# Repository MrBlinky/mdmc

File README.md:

# MDMC - Menu Driven Multi Cart

A Menu driven Multi Cart for the Atari 2600 made out of a few descrete logic chips and a (E)EPROM or FLASH memory.

Boards can be ordered from [OSH Park](https://oshpark.com/shared_projects/qgWffwwL) or you can create your own using the Eagle board file.

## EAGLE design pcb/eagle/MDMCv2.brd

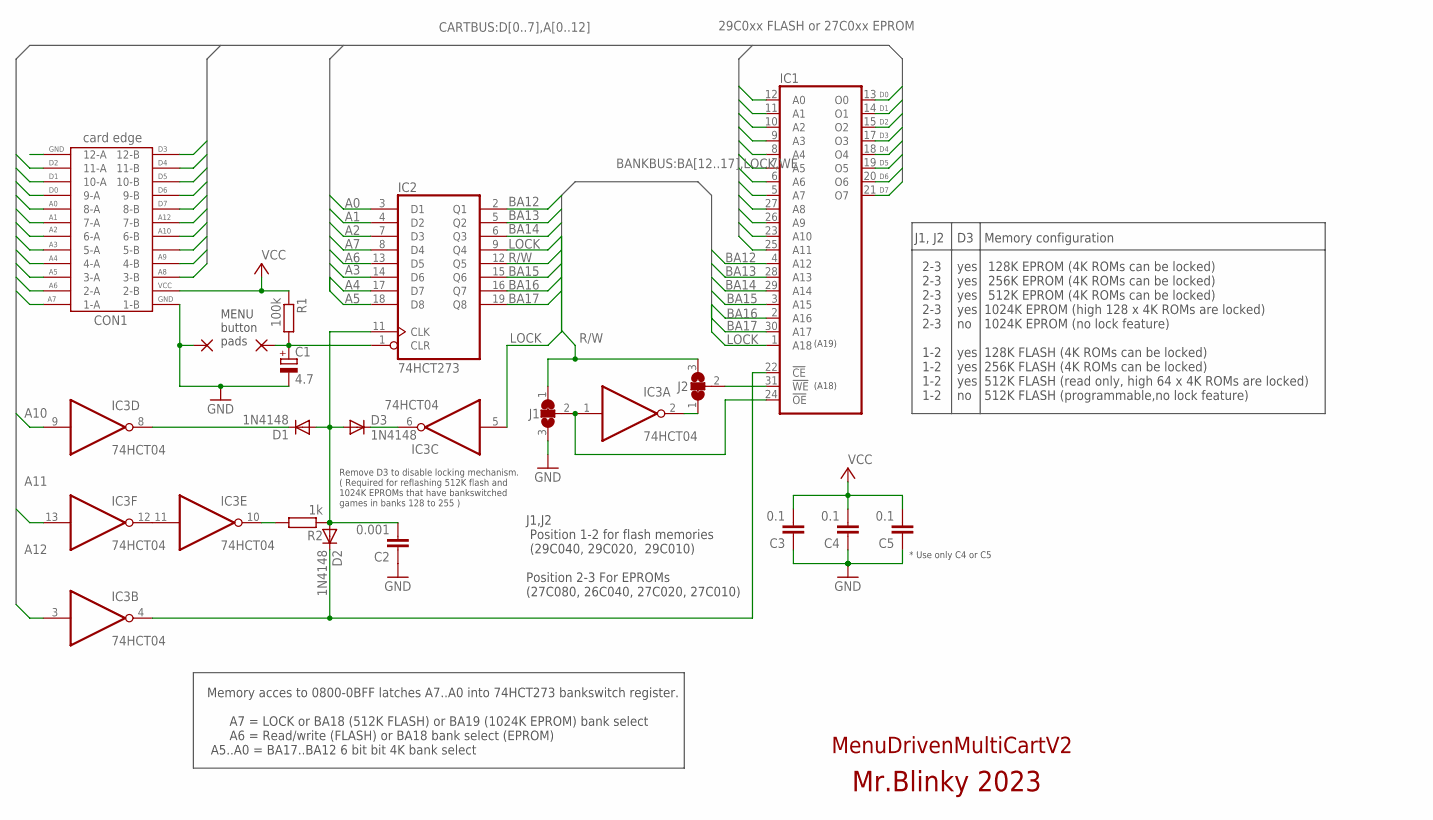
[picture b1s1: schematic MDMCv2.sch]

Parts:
C1: 4.7; TT2D5L
C2: 0.001; C050-025X075
C3, C4, C5: 0.1; C050-025X075
CON1: card edge; 24PINEDGE-254MM
D1, D2, D3: 1N4148; DO35-7
IC1: 29C0xx FLASH or 27C0xx EPROM; DIL32
IC2: 74HCT273; DIL20
IC3: 74HCT04; DIL14
J1, J2: SJ2W; SJ_2
MB1, MB2: WIREPAD1,6/0,9; 1,6/0,9
R1: 100k; 0207/7
R2: 1k; 0207/7

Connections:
!RESET: C1.+, IC2.1 (CLR), MB1.1, R1.2
/A10: D1.C, IC3.8 (O)
/A11: IC3.11 (I), IC3.12 (O)
/CE: D2.C, IC1.22 (!CE), IC3.4 (O)
/LOCK: D3.C, IC3.6 (O)
/OE: IC1.24 (!OE), IC3.1 (I), J1.2
/WE: IC1.31 (!WE), J2.2
/WEJ2: IC3.2 (O), J2.1
A0: CON1.8-A, IC1.12 (A0), IC2.3 (D1)
A1: CON1.7-A, IC1.11 (A1), IC2.4 (D2)
A2: CON1.6-A, IC1.10 (A2), IC2.7 (D3)
A3: CON1.5-A, IC1.9 (A3), IC2.14 (D6)
A4: CON1.4-A, IC1.8 (A4), IC2.17 (D7)
A5: CON1.3-A, IC1.7 (A5), IC2.18 (D8)
A6: CON1.2-A, IC1.6 (A6), IC2.13 (D5)
A7: CON1.1-A, IC1.5 (A7), IC2.8 (D4)
A8: CON1.3-B, IC1.27 (A8)
A9: CON1.4-B, IC1.26 (A9)
A10: CON1.6-B, IC1.23 (A10), IC3.9 (I)
A11: CON1.5-B, IC1.25 (A11), IC3.13 (I)
A11B: IC3.10 (O), R2.2
A12: CON1.7-B, IC3.3 (I)
BA12: IC1.4 (A12), IC2.2 (Q1)
BA13: IC1.28 (A13), IC2.5 (Q2)
BA14: IC1.29 (A14), IC2.6 (Q3)
BA15: IC1.3 (A15), IC2.15 (Q6)
BA16: IC1.2 (A16), IC2.16 (Q7)
BA17: IC1.30 (A17), IC2.19 (Q8)
CLK: C2.2, D1.A, D2.A, D3.A, IC2.11 (CLK), R2.1
D0: CON1.9-A, IC1.13 (O0)
D1: CON1.10-A, IC1.14 (O1)
D2: CON1.11-A, IC1.15 (O2)
D3: CON1.12-B, IC1.17 (O3)
D4: CON1.11-B, IC1.18 (O4)
D5: CON1.10-B, IC1.19 (O5)
D6: CON1.9-B, IC1.20 (O6)
D7: CON1.8-B, IC1.21 (O7)
GND: C1.-, C2.1, C3.1, C4.1, C5.1, CON1.1-B, CON1.12-A, IC1.16 (GND), IC2.10 (GND), IC3.7 (GND), J1.3, MB2.1
LOCK: IC1.1 (A18), IC2.9 (Q4), IC3.5 (I)
R/W: IC2.12 (Q5), J1.1, J2.3
VCC: C3.2, C4.2, C5.2, CON1.2-B, IC1.32 (VCC), IC2.20 (VCC), IC3.14 (VCC), R1.1

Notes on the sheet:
J1,J2 Position 1-2 for flash memories (29C040, 29C020, 29C010) Position 2-3 For EPROMs (27C080, 26C040, 27C020, 27C010)
MENU button pads
* Use only C4 or C5
Remove D3 to disable locking mechanism. ( Required for reflashing 512K flash and 1024K EPROMs that have bankswitched games in banks 128 to 255 )
MenuDrivenMultiCartV2
Mr.Blinky 2023
Memory acces to 0800-0BFF latches A7..A0 into 74HCT273 bankswitch register. A7 = LOCK or BA18 (512K FLASH) or BA19 (1024K EPROM) bank select A6 = Read/write (FLASH) or BA18 bank select (EPROM) A5..A0 = BA17..BA12 6 bit bit 4K bank select
(A18)
(A19)
Memory configuration 128K EPROM (4K ROMs can be locked) 256K EPROM (4K ROMs can be locked) 512K EPROM (4K ROMs can be locked) 1024K EPROM (high 128 x 4K ROMs are locked) 1024K EPROM (no lock feature) 128K FLASH (4K ROMs can be locked) 256K FLASH (4K ROMs can be locked) 512K FLASH (read only, high 6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
J1, J2 2-3 2-3 2-3 2-3 2-3 1-2 1-2 1-2 1-2
D3 yes yes yes yes no yes yes yes no

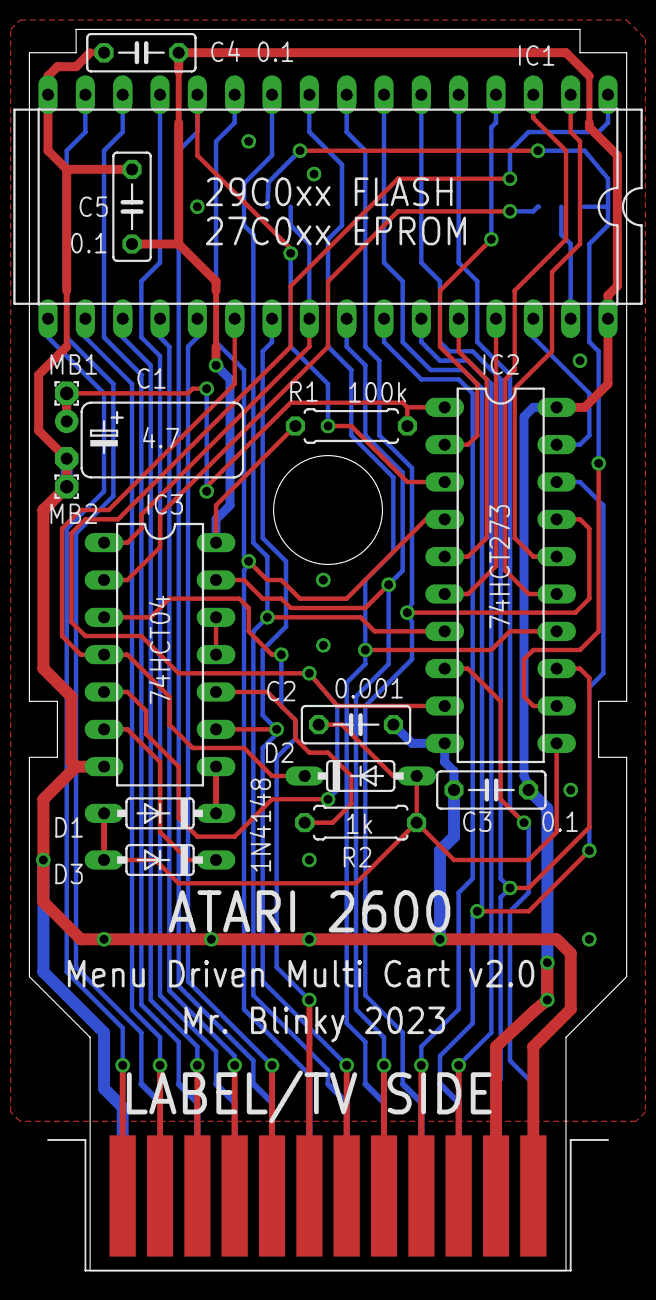
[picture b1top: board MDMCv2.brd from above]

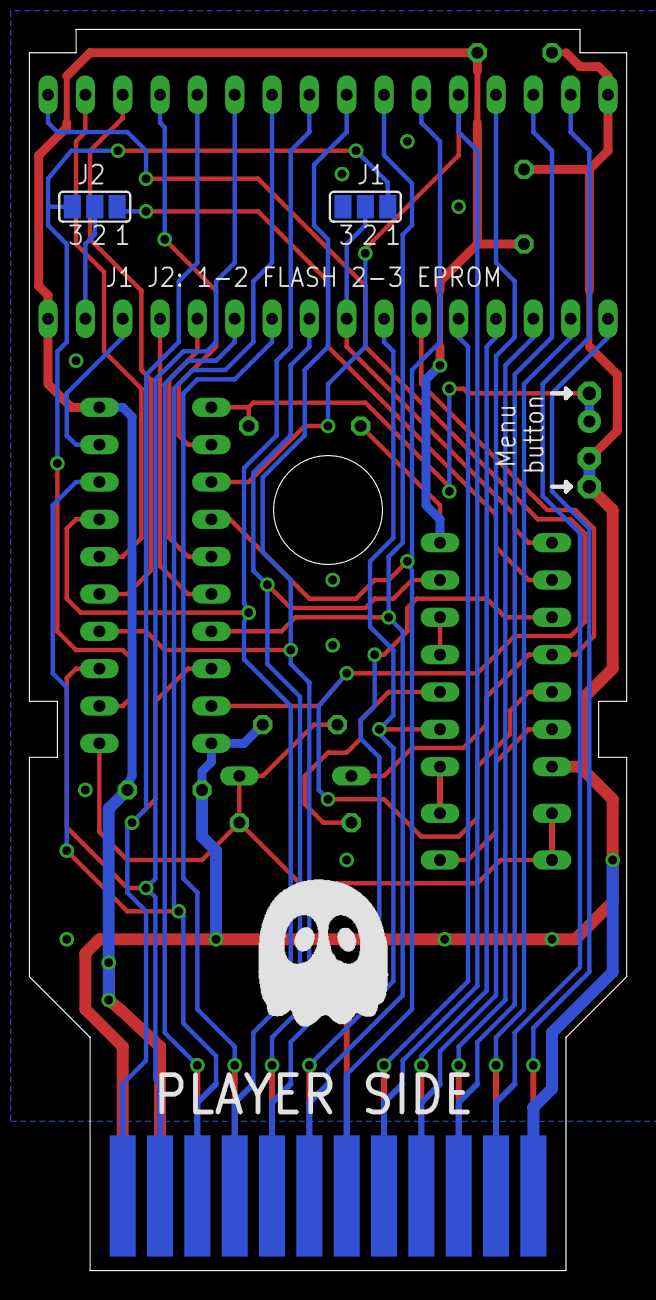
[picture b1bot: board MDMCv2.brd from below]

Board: 2 copper layers, 40.6 x 84.5 mm, 18 parts (3 on the bottom side), 41 nets.
